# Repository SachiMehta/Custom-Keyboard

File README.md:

# Custom-Keyboard

## 📌 Status
Testing and Research Stage

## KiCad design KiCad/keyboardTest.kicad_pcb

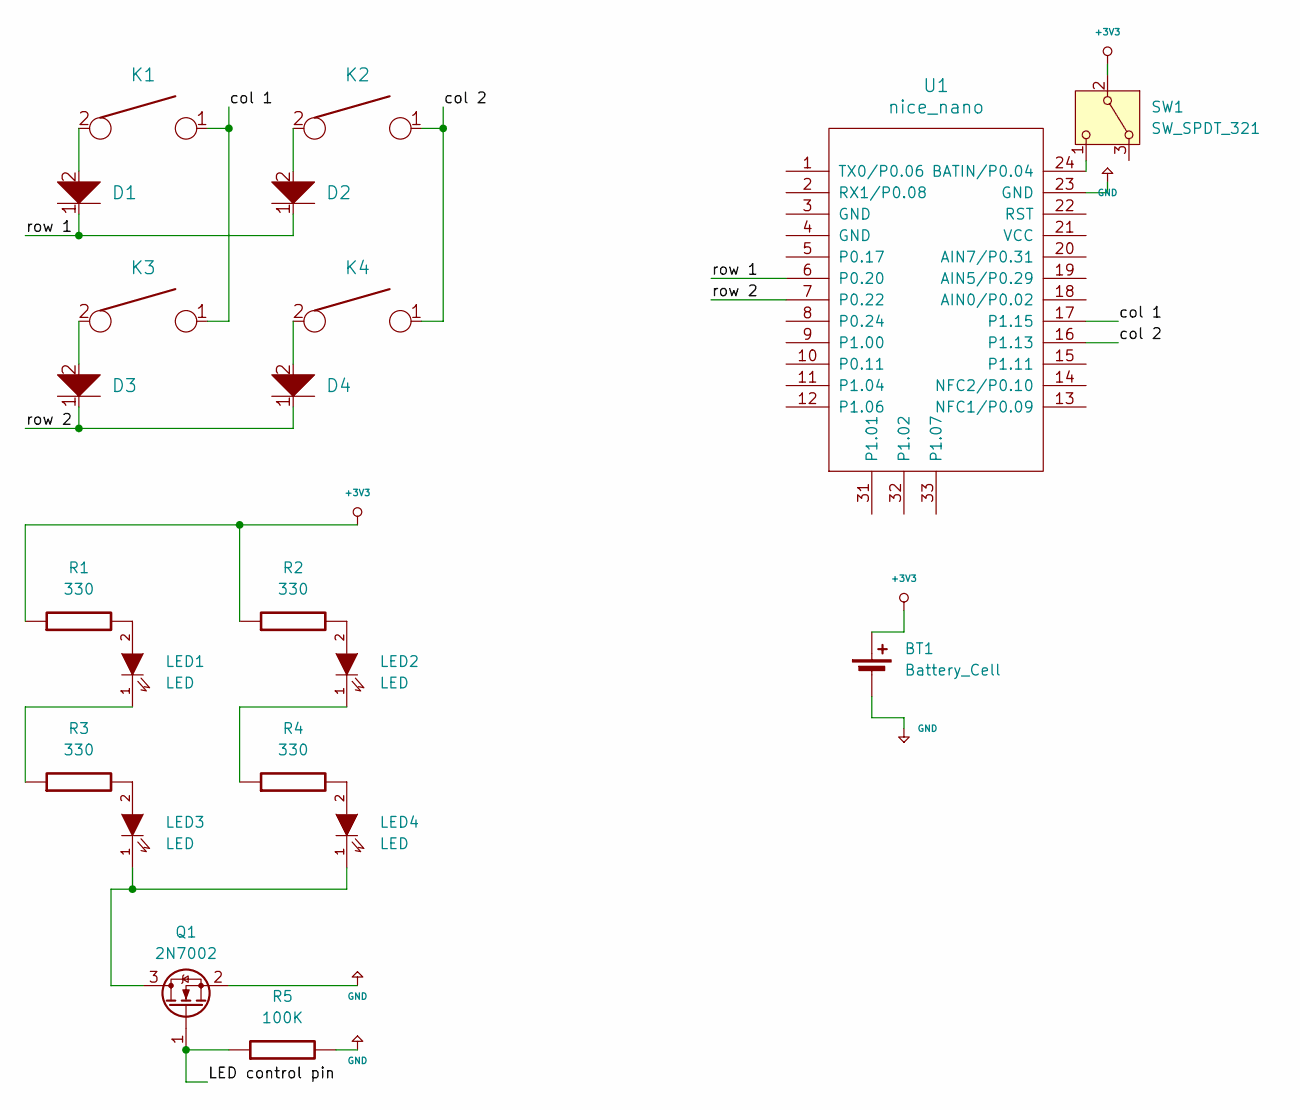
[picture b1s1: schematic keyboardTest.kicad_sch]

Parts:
BT1: Battery_Cell; JST_S2B-PH-SM4-TB
D1, D2, D3, D4: D; D_SOD123
K1, K2, K3, K4: KEYSW; Kailh_socket_MX
LED1, LED2, LED3, LED4: LED; LED_TH
Q1: 2N7002; SOT-23
R1, R2, R3, R4: 330; R_1608
R5: 100K; R_1608
SW1: SW_SPDT_321; Nidec_Copal_CAS-120A
U1: nice_nano

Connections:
+3V3: BT1.1 (+), R1.1, R2.1, SW1.2 (B)
/LED control pin: Q1.1 (G), R5.1
/col 1: K1.1, K3.1, U1.17 (P1.15)
/col 2: K2.1, K4.1, U1.16 (P1.13)
/row 1: D1.1, D2.1, U1.6 (P0.20)
/row 2: D3.1, D4.1, U1.7 (P0.22)
GND: BT1.2 (-), Q1.2 (S), R5.2, U1.23 (GND)
unnamed: D1.2, K1.2
unnamed: D2.2, K2.2
unnamed: D3.2, K3.2
unnamed: D4.2, K4.2
unnamed: LED1.2 (A), R1.2
unnamed: LED1.1 (K), R3.1
unnamed: LED2.2 (A), R2.2
unnamed: LED2.1 (K), R4.1
unnamed: LED3.2 (A), R3.2
unnamed: LED3.1 (K), LED4.1 (K), Q1.3 (D)
unnamed: LED4.2 (A), R4.2
unnamed: SW1.1 (C), U1.24 (BATIN/P0.04)

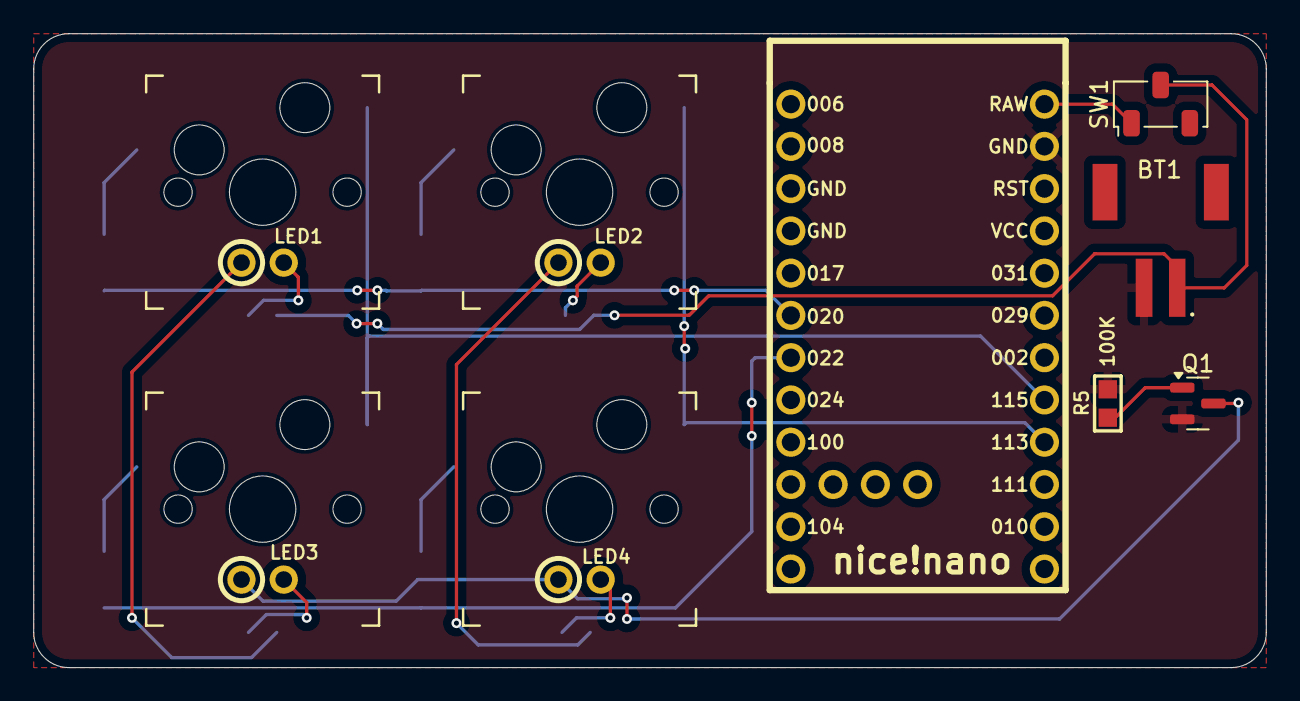
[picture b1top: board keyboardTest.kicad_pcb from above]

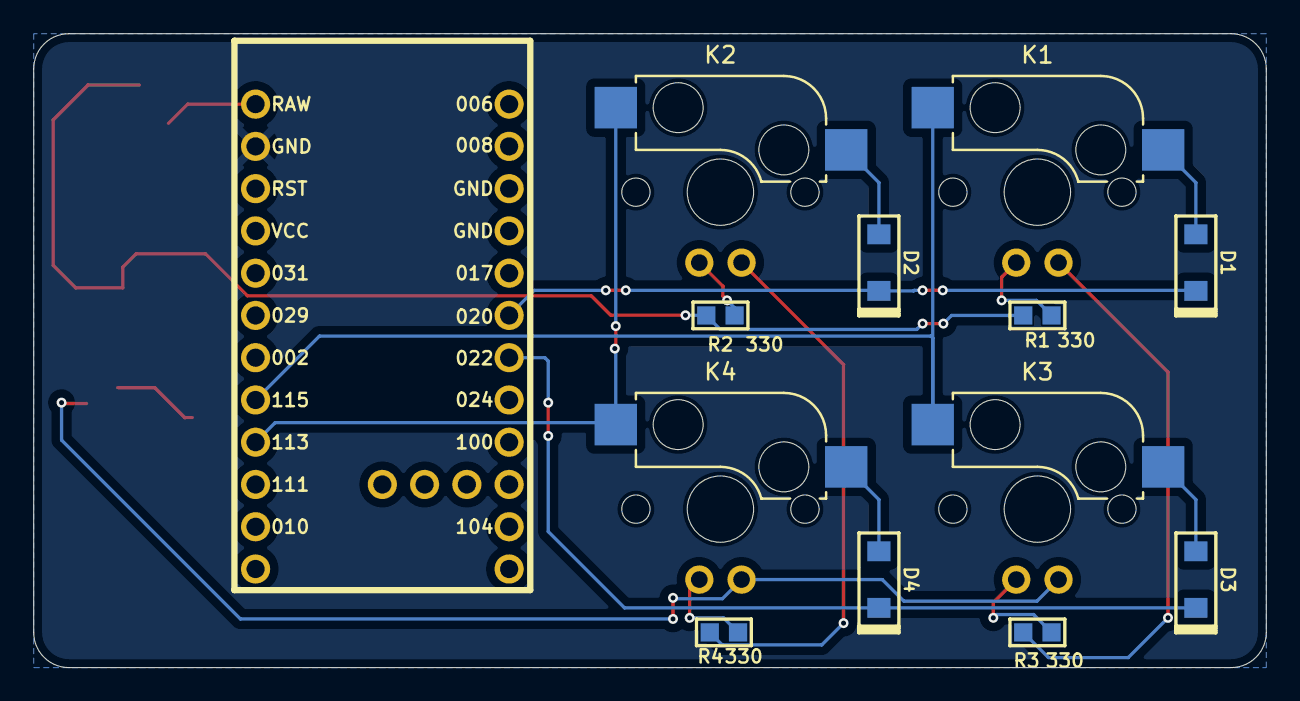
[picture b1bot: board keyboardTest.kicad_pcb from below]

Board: 2 copper layers, 74.1 x 38.1 mm, 21 parts (8 on the bottom side), 19 nets.

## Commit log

2025-12-30 move
